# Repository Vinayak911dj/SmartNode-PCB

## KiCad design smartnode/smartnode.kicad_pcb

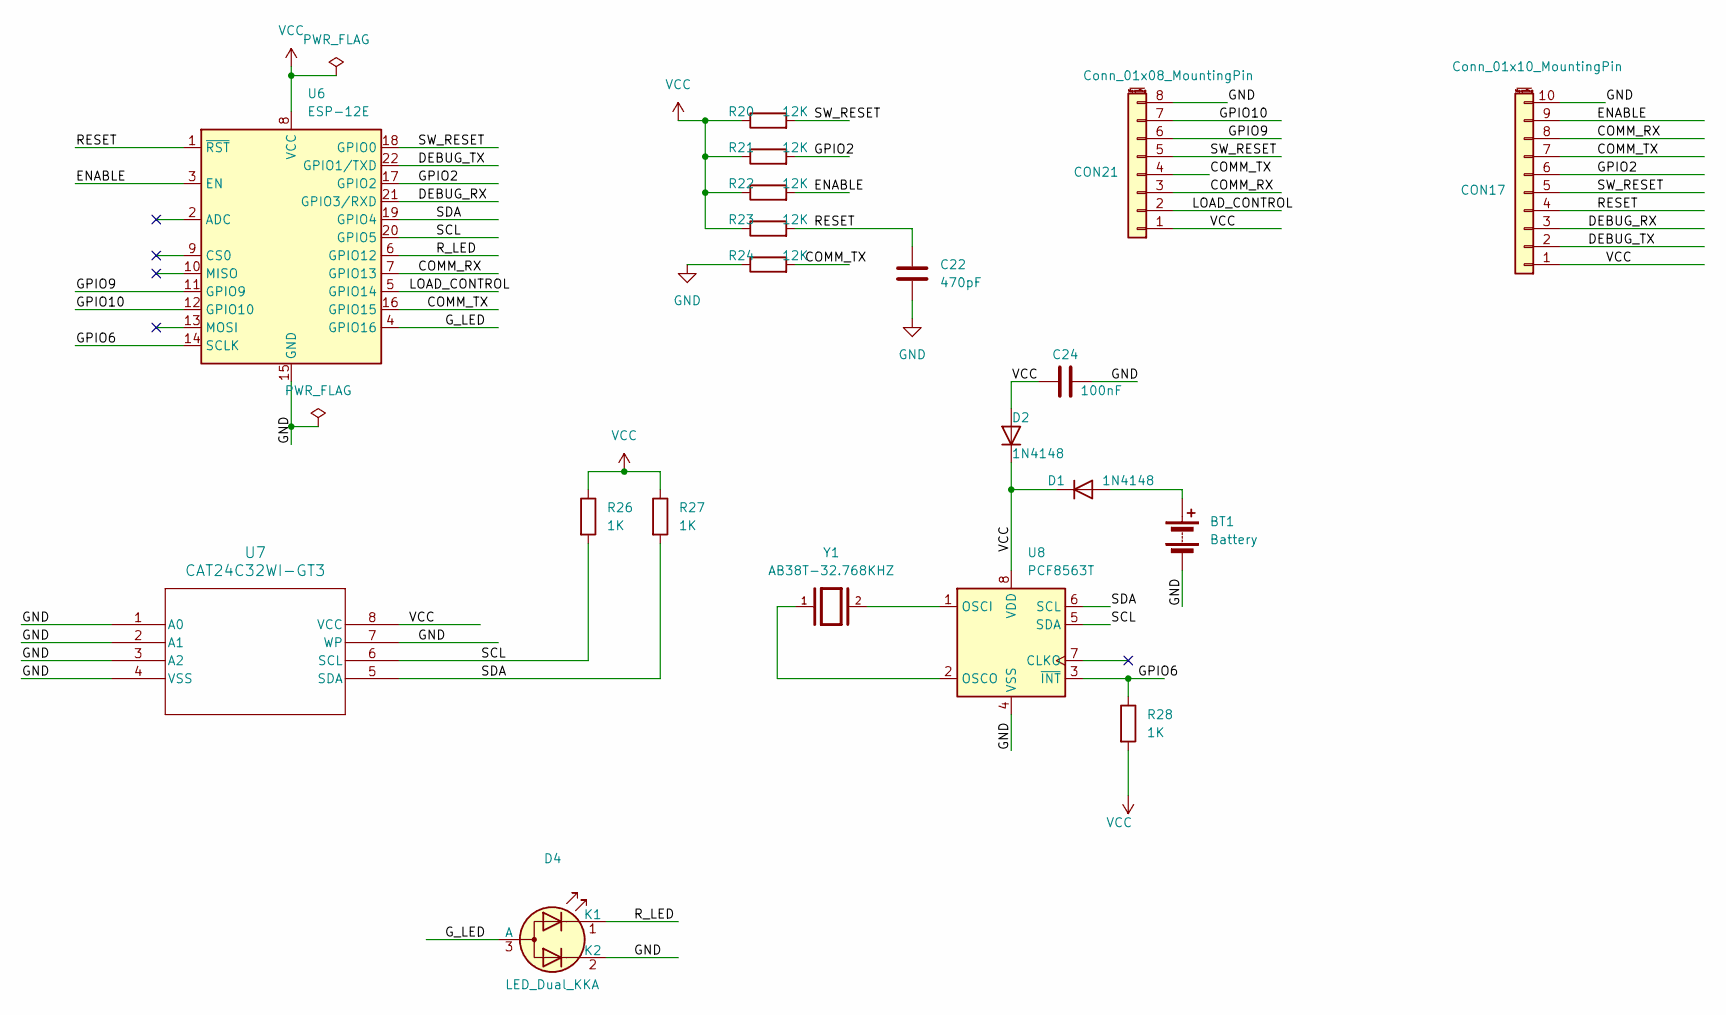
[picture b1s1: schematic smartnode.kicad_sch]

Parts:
BT1: Battery; BatteryHolder_MPD_BC2003_1x2032
C22: 470pF; C_0805_2012Metric
C24: 100nF; C_0805_2012Metric
CON17: Conn_01x10_MountingPin; PinSocket_1x10_P2.54mm_Vertical
CON21: Conn_01x08_MountingPin; PinSocket_1x08_P2.54mm_Vertical
D1, D2: 1N4148; LED_D2.0mm_W4.8mm_H2.5mm_FlatTop
D4: LED_Dual_KKA; LED_Rectangular_W5.0mm_H2.0mm-3Pins
R20, R21, R22, R23, R24: 12K; R_0805_2012Metric
R26, R27, R28: 1K; R_0805_2012Metric
U6: ESP-12E
U7: CAT24C32WI-GT3; SOIC8_ONS
U8: PCF8563T; SOIC-8_3.9x4.9mm_P1.27mm
Y1: AB38T-32.768KHZ; XTAL_AB38T-32.768KHZ

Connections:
/COMM_RX: CON17.8, CON21.3, U6.7 (GPIO13)
/COMM_TX: CON17.7, CON21.4, R24.2, U6.16 (GPIO15)
/DEBUG_RX: CON17.3, U6.21 (GPIO3/RXD)
/DEBUG_TX: CON17.2, U6.22 (GPIO1/TXD)
/ENABLE: CON17.9, R22.2, U6.3 (EN)
/GPIO2: CON17.6, R21.2, U6.17 (GPIO2)
/GPIO6: R28.1, U6.14 (SCLK), U8.3 (~INT)
/GPIO9: CON21.6, U6.11 (GPIO9)
/GPIO10: CON21.7, U6.12 (GPIO10)
/G_LED: D4.3 (A), U6.4 (GPIO16)
/LOAD_CONTROL: CON21.2, U6.5 (GPIO14)
/RESET: C22.1, CON17.4, R23.2, U6.1 (~RST)
/R_LED: D4.1 (K1), U6.6 (GPIO12)
/SCL: R26.2, U6.20 (GPIO5), U7.6 (SCL), U8.5 (SDA)
/SDA: R27.2, U6.19 (GPIO4), U7.5 (SDA), U8.6 (SCL)
/SW_RESET: CON17.5, CON21.5, R20.2, U6.18 (GPIO0)
GND: BT1.2 (-), C22.2, C24.2, CON17.10, CON21.8, D4.2 (K2), R24.1, U6.15 (GND), U7.1 (A0), U7.2 (A1), U7.3 (A2), U7.4 (VSS), U7.7 (WP), U8.4 (VSS)
unnamed: BT1.1 (+), D1.2 (A)
unnamed: U8.1 (OSCI), Y1.2
unnamed: U8.2 (OSCO), Y1.1
VCC: C24.1, CON17.1, CON21.1, D1.1 (K), D2.1 (K), D2.2 (A), R20.1, R21.1, R22.1, R23.1, R26.1, R27.1, R28.2, U6.8 (VCC), U7.8 (VCC), U8.8 (VDD)

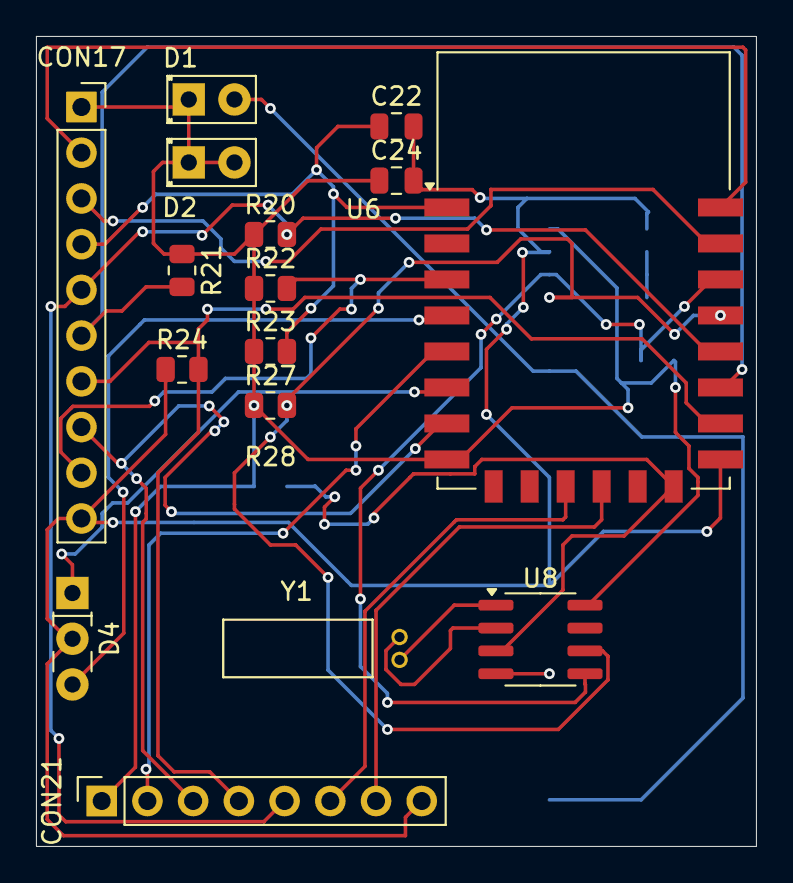
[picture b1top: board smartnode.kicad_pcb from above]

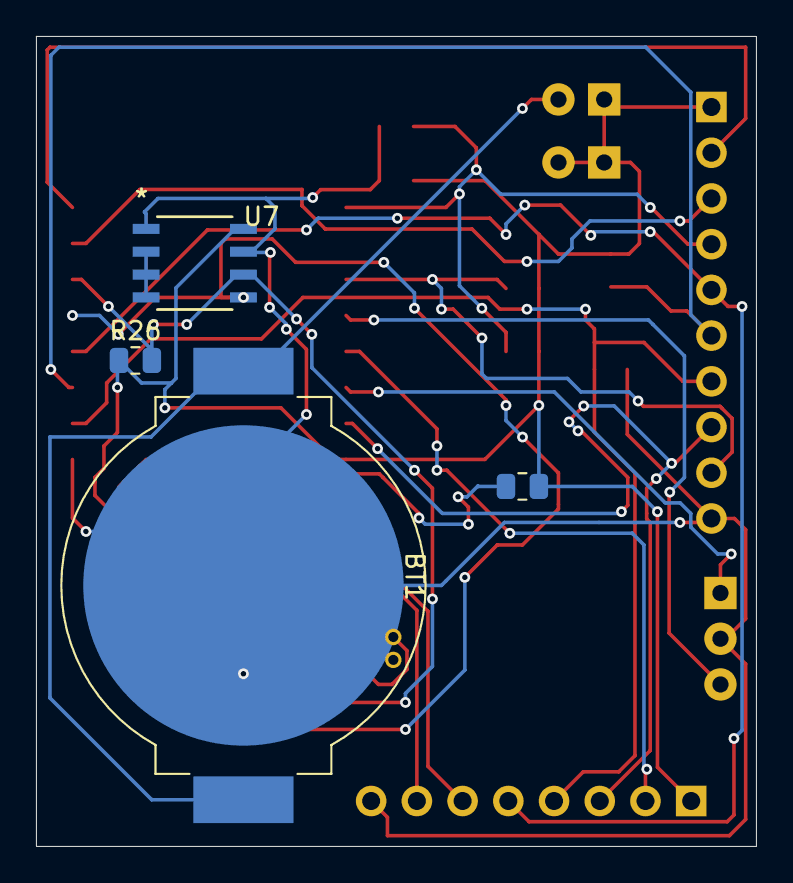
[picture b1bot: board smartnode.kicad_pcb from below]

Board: 2 copper layers, 40.0 x 45.0 mm, 20 parts (4 on the bottom side), 21 nets.
